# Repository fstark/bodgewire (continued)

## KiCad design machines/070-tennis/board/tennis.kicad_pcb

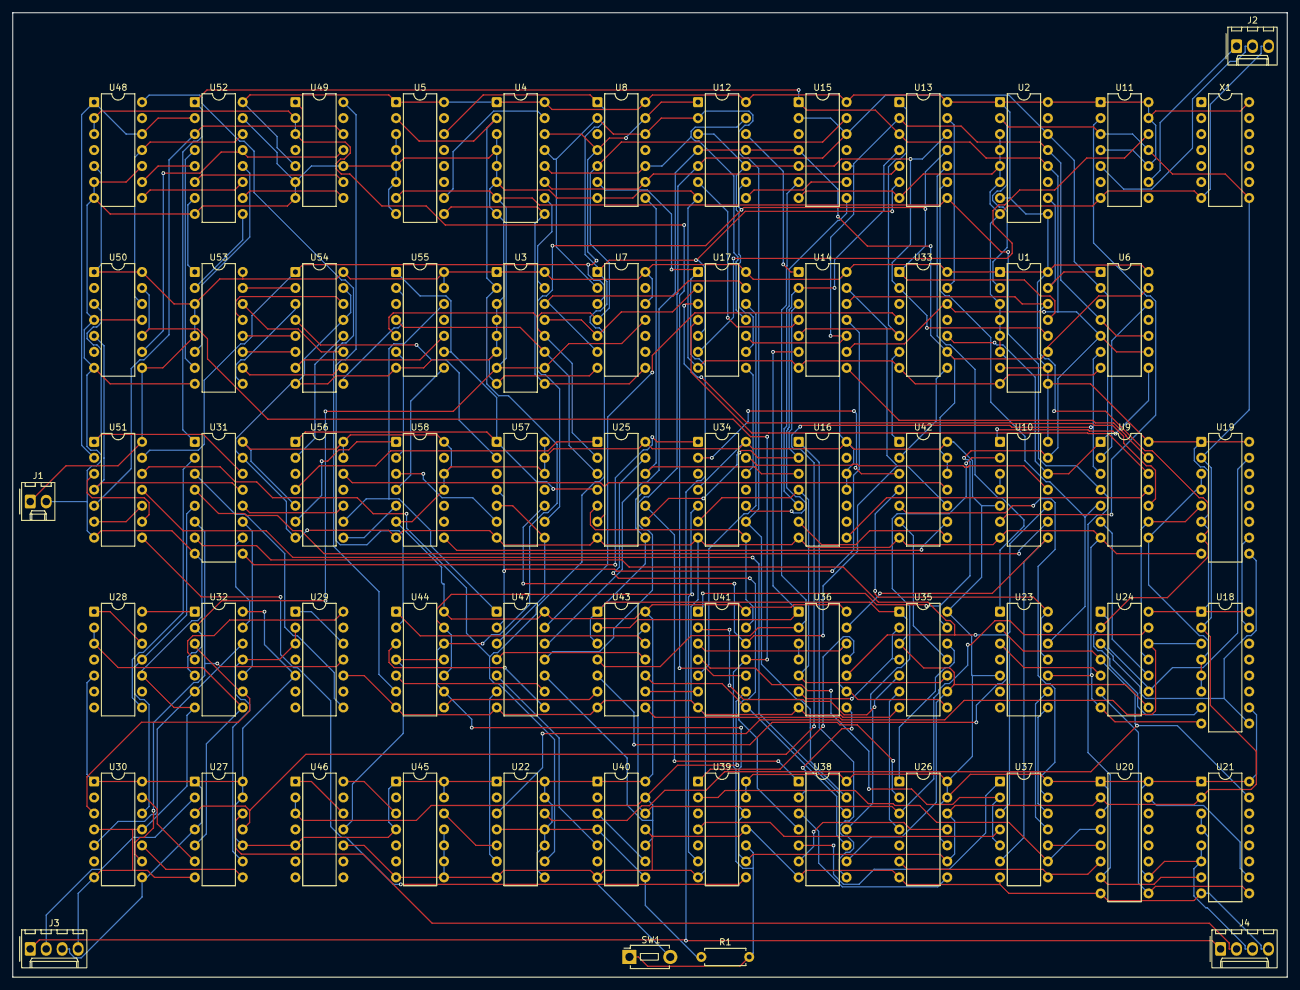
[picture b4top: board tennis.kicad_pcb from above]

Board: 2 copper layers, 202.6 x 153.3 mm, 65 parts (0 on the bottom side), 184 nets.

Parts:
J1: POWER; Molex_KK-254_AE-6410-02A_1x02_P2.54mm_Vertical
J2: VIDEO; Molex_KK-254_AE-6410-03A_1x03_P2.54mm_Vertical
J3, J4: PADDLE; Molex_KK-254_AE-6410-04A_1x04_P2.54mm_Vertical
R1: 1k; R_Axial_DIN0207_L6.3mm_D2.5mm_P7.62mm_Horizontal
SW1: BUTTON; SW_PUSH_1P1T_6x3.5mm_H5.0_APEM_MJTP1250
U1, U2, U3, U4, U5, U18, U19, U20, U21: 74LS161; DIP-16_W7.62mm
U6, U8, U15, U33, U34, U55, U56, U57: 74LS20; DIP-14_W7.62mm
U7, U16, U58: 74LS30; DIP-14_W7.62mm
U9, U41: 74LS04; DIP-14_W7.62mm
U10: 74LS86; DIP-14_W7.62mm
U11, U27: 74LS74; DIP-14_W7.62mm
U12, U17, U35, U43: 74LS27; DIP-14_W7.62mm
U13, U25, U32, U37, U47: 74LS02; DIP-14_W7.62mm
U14, U24, U42, U51: 74LS00; DIP-14_W7.62mm
U22, U26, U30, U39, U40, U44, U45, U50: 74LS107; DIP-14_W7.62mm
U23, U28, U29, U46: 74LS93; DIP-14_W7.62mm
U31, U52, U54: 74LS157; DIP-16_W7.62mm
U36: 74LS08; DIP-14_W7.62mm
U38: 74LS32; DIP-14_W7.62mm
U48, U49: 74LS90; DIP-14_W7.62mm
U53: 74LS48; DIP-16_W7.62mm
X1: OSC; DIP-14_W7.62mm

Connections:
A_TOP: U54.12 (4Y), U56.2 (1B)
BALLV_N: U16.1 (A), U38.8 (3Y)
BALL_CK: U13.10 (3Y), U23.1 (CKB)
BALL_N: U24.8 (3Y), U25.8 (3A), U25.11 (4A), U35.1 (1A), U35.3 (2A), U35.9 (3A), U38.9 (3A), U43.1 (1A), U43.3 (2A)
BALL_OFF: U9.5 (3A), U13.9 (3B), U23.12 (QA)
BALL_QB: U23.9 (QB), U37.11 (4A)
BALL_QC: U23.8 (QC), U37.12 (4B)
BALL_QD: U23.11 (QD), U23.14 (CKA), U42.4 (2A)
BC: U54.7 (2Y), U55.10 (2B)
BHC: U18.15 (RCO), U19.10 (ENT)
BOTTOM_N: U8.8 (2Y), U16.3 (C), U25.12 (4B)
BV8: U22.3 (1Q), U23.3 (R02), U24.5 (2B)
BVC: U20.15 (RCO), U21.10 (ENT)
CLK: U1.2 (CLK), U2.2 (CLK), U3.2 (CLK), U4.2 (CLK), U5.2 (CLK), U11.3 (1CLK), U11.11 (2CLK), U18.2 (CLK), U19.2 (CLK), U20.2 (CLK), U21.2 (CLK), U26.9 (2CLK), U26.12 (1CLK), U39.9 (2CLK), U39.12 (1CLK), U44.9 (2CLK), U44.12 (1CLK), X1.8 (OUT)
COL3: U47.1 (1Y), U55.12 (2C), U56.9 (2A)
COL_L_N: U33.6 (1Y), U42.1 (1A)
COL_R_N: U33.8 (2Y), U42.2 (1B)
FAST: U40.5 (2Q), U47.5 (2A)
FE: U54.4 (1Y), U57.2 (1B)
FRAME0: U22.5 (2Q), U45.12 (1CLK)
FRAME0_N: U22.6 (2Q_N), U47.6 (2B)
FRAME1: U45.3 (1Q), U46.14 (CKA)
FRAME_END_N: U3.9 (LOAD_N), U4.9 (LOAD_N), U5.9 (LOAD_N), U7.8 (Y)
GD: U54.9 (3Y), U55.2 (1B)
GLYPH: U42.9 (3A), U58.8 (Y)
GND: J1.2 (GND), J2.3 (GND), J3.4 (GND), J4.4 (GND), SW1.2, U1.3 (A), U1.4 (B), U1.5 (C), U1.6 (D), U1.8 (GND), U2.3 (A), U2.4 (B), U2.5 (C), U2.6 (D), U2.8 (GND), U3.3 (A), U3.4 (B), U3.5 (C), U3.6 (D), U3.8 (GND), U4.3 (A), U4.4 (B), U4.5 (C), U4.6 (D), U4.8 (GND), U5.3 (A), U5.4 (B), U5.5 (C), U5.6 (D), U5.8 (GND), U6.7 (GND), U7.7 (GND), U8.7 (GND), U9.7 (GND), U10.7 (GND), U11.7 (GND), U12.7 (GND), U13.7 (GND), U14.7 (GND), U15.7 (GND), U16.7 (GND), U17.7 (GND), U18.8 (GND), U19.8 (GND), U20.8 (GND), U21.3 (A), U21.4 (B), U21.8 (GND), U22.7 (GND), U23.10 (GND), U24.7 (GND), U25.7 (GND), U26.7 (GND), U27.7 (GND), U28.10 (GND), U29.10 (GND), U30.4 (1K), U30.7 (GND), U30.11 (2K), U31.8 (GND), U31.15 (G_N), U32.7 (GND), U33.7 (GND), U34.7 (GND), U35.7 (GND), U36.7 (GND), U37.7 (GND), U38.7 (GND), U39.7 (GND), U39.11 (2K), U40.7 (GND), U40.11 (2K), U41.7 (GND), U42.7 (GND), U43.7 (GND), U44.7 (GND), U45.7 (GND), U45.8 (2J), U45.9 (2CLK), U45.10 (2CLR_N), U45.11 (2K), U46.10 (GND), U47.7 (GND), U48.6 (R91), U48.7 (R92), U48.10 (GND), U49.6 (R91), U49.7 (R92), U49.10 (GND), U50.4 (1K), U50.7 (GND), U50.11 (2K), U51.7 (GND), U52.8 (GND), U52.15 (G_N), U53.8 (GND), U54.8 (GND), U54.13 (4B), U54.15 (G_N), U55.7 (GND), U56.7 (GND), U57.7 (GND), U58.7 (GND), X1.7 (GND)
GO_DOWN: U26.8 (2J), U38.3 (1Y)
GO_LEFT: U26.4 (1K), U35.6 (2Y)
GO_RIGHT: U26.1 (1J), U35.12 (1Y)
GO_UP: U26.11 (2K), U38.6 (2Y)
H0: U1.14 (QA), U14.12 (4A), U18.7 (ENP), U19.7 (ENP), U24.2 (1B)
H1: U1.13 (QB), U12.9 (3A), U13.11 (4A), U33.1 (1A), U57.9 (2A)
H2: U1.12 (QC), U12.3 (2A), U12.10 (3B), U13.12 (4B), U15.5 (1D), U17.9 (3A), U33.2 (1B)
H3: U1.11 (QD), U6.13 (2D), U12.4 (2B), U12.11 (3C), U15.4 (1C), U33.9 (2A), U42.12 (4A), U42.13 (4B), U47.12 (4B)
H3_N: U25.6 (2B), U42.11 (4Y), U56.12 (2C)
H4: U2.14 (QA), U6.2 (1B), U9.1 (1A), U10.12 (4A), U12.5 (2C), U15.2 (1B), U15.12 (2C), U33.10 (2B), U47.11 (4A)
H4_N: U6.12 (2C), U9.2 (1Y)
H5: U2.13 (QB), U6.4 (1C), U6.10 (2B), U13.2 (1A), U14.10 (3B), U15.10 (2B), U17.10 (3B)
H6: U2.12 (QC), U6.5 (1D), U6.9 (2A), U10.13 (4B), U13.3 (1B), U14.9 (3A), U15.1 (1A), U31.1 (S), U33.12 (2C), U35.13 (1C), U41.1 (1A), U52.1 (S)
H6_N: U35.5 (2C), U41.2 (1Y)
H12_LOW: U13.13 (4Y), U33.13 (2D)
H34_LOW: U33.4 (1C), U47.13 (4Y)
H56_LOW: U13.1 (1Y), U14.5 (2B), U33.5 (1D)
HBALL: U19.15 (RCO), U24.1 (1A), U24.9 (3A)
HBLANK: U9.12 (6Y), U17.4 (2B)
HBLANK_N: U9.13 (6A), U14.8 (3Y)
HC: U1.15 (RCO), U2.10 (ENT), U6.1 (1A)
HDIR: U24.13 (4B), U26.3 (1Q), U40.12 (1CLK), U43.13 (1C)
HDIR_N: U26.2 (1Q_N), U43.5 (2C)
HIT_BOTTOM: U25.13 (4Y), U38.4 (2A)
HIT_HIGH: U37.1 (1Y), U38.5 (2B)
HIT_LOW: U36.8 (3Y), U38.2 (1B)
HIT_TOP: U25.10 (3Y), U38.1 (1A)
HLOAD_N: U18.9 (LOAD_N), U19.9 (LOAD_N), U24.3 (1Y)
HMOVE: U18.3 (A), U24.12 (4A), U43.8 (3Y)
HSYNC_N: U6.8 (2Y), U10.1 (1A)
HX: U10.11 (4Y), U34.13 (2D)
LDONE: U30.3 (1Q), U32.3 (1B), U32.9 (3B)
LEFT_A: U12.6 (2Y), U14.4 (2A)
LEFT_N: U14.6 (2Y), U36.1 (1A), U43.2 (1B)
LINE_END: U3.7 (ENP), U3.10 (ENT), U4.7 (ENP), U5.7 (ENP), U7.11 (G), U9.4 (2Y), U13.8 (3A), U20.7 (ENP), U21.7 (ENP), U32.2 (1A), U32.5 (2A)
LINE_END_N: U6.6 (1Y), U9.3 (2A), U27.3 (1CLK), U27.11 (2CLK)
LOST_LEFT: U44.3 (1Q), U47.8 (3A)
LOST_LEFT_N: U44.2 (1Q_N), U49.14 (CKA)
LOST_RIGHT: U44.5 (2Q), U47.9 (3B)
LOST_RIGHT_N: U44.6 (2Q_N), U48.14 (CKA)
LP0: U28.1 (CKB), U28.12 (QA)
LP2: U28.8 (QC), U31.2 (1A)
LP3: U28.11 (QD), U30.12 (1CLK), U31.5 (2A)
LPADV: U31.11 (3A), U32.10 (3Y)
LPAD_CK: U28.14 (CKA), U32.1 (1Y)
LPULSE: J3.2 (OUT), U27.2 (1D)
LWAIT: U27.5 (1Q), U28.2 (R01), U28.3 (R02), U32.8 (3A)
LWAIT_N: U27.6 (1Q_N), U30.13 (1CLR_N)
MID_A: U37.13 (4Y), U42.5 (2B)
MID_N: U35.11 (3C), U42.6 (2Y)
MISS_LEFT: U43.12 (1Y), U44.1 (1J)
MISS_RIGHT: U43.6 (2Y), U44.8 (2J)
MIX: U9.11 (5A), U16.8 (Y)
MIX_N: U9.10 (5Y), U17.3 (2A)
MOVE: U17.12 (1Y), U41.5 (3A)
MOVE_N: U41.6 (3Y), U43.9 (3A)
MR: U9.8 (4Y), U18.4 (B), U18.5 (C), U18.6 (D), U19.3 (A), U19.4 (B)
MR_N: U9.9 (4A), U19.5 (C), U24.11 (4Y)
NET_A: U12.8 (3Y), U15.9 (2A)
NET_N: U15.8 (2Y), U16.5 (E)
PADV: U31.9 (3Y), U34.1 (1A)
PAD_HIT: U35.8 (3Y), U36.9 (3A), U36.12 (4A), U41.3 (2A)
PAD_HIT_N: U37.2 (1A), U37.5 (2A), U41.4 (2Y)
PAD_N: U16.4 (D), U34.6 (1Y), U35.10 (3B), U36.5 (2B)
PCOL: U34.2 (1B), U42.3 (1Y)
PLAY: U34.5 (1D), U39.6 (2Q_N), U44.10 (2CLR_N), U44.13 (1CLR_N)
QH0_N: U14.11 (4Y), U47.2 (1A), U57.4 (1C)
QH1_N: U47.3 (1B), U57.5 (1D), U57.8 (2Y)
RDONE: U30.5 (2Q), U32.6 (2B), U32.12 (4B)
REGION: U14.13 (4B), U41.12 (6Y), U42.10 (3B), U57.10 (2B)
REGION_N: U25.5 (2A), U34.8 (2Y), U41.13 (6A)
RIGHT_N: U15.6 (1Y), U36.2 (1B), U43.4 (2B)
RP0: U29.1 (CKB), U29.12 (QA)
RP2: U29.8 (QC), U31.3 (1B)
RP3: U29.11 (QD), U30.9 (2CLK), U31.6 (2B)
RPADV: U31.10 (3B), U32.13 (4Y)
RPAD_CK: U29.14 (CKA), U32.4 (2Y)
RPULSE: J4.2 (OUT), U27.12 (2D)
RWAIT: U27.9 (2Q), U29.2 (R01), U29.3 (R02), U32.11 (4A)
RWAIT_N: U27.8 (2Q_N), U30.10 (2CLR_N)
SC0: U52.4 (1Y), U53.7 (A)
SC1: U52.7 (2Y), U53.1 (B)
SC2: U52.9 (3Y), U53.2 (C)
SC3: U52.12 (4Y), U53.6 (D)
SCORE_A: U17.8 (3Y), U34.12 (2C)
SCORE_N: U16.6 (F), U42.8 (3Y)
SEG_A: U53.13 (SA), U54.14 (4A)
SEG_B: U53.12 (SB), U54.5 (2A)
SEG_C: U53.11 (SC), U54.6 (2B)
SEG_D: U53.10 (SD), U54.10 (3B)
SEG_E: U53.9 (SE), U54.3 (1B)
SEG_F: U53.15 (SF), U54.2 (1A)
SEG_G: U53.14 (SG), U54.11 (3A)
SERVE_END: U44.4 (1K), U44.11 (2K), U46.11 (QD)
SERVING: U38.10 (3B), U41.8 (4Y), U43.10 (3B)
SERVING_N: U40.10 (2CLR_N), U40.13 (1CLR_N), U41.9 (4A), U46.2 (R01), U46.3 (R02), U47.10 (3Y)
SET_SHALLOW: U36.11 (4Y), U39.1 (1J)
SET_STEEP: U37.4 (2Y), U39.4 (1K)
SIDES_N: U36.3 (1Y), U36.4 (2A)
SKIP: U43.11 (3C), U47.4 (2Y)
SL0: U48.1 (CKB), U48.12 (QA), U51.2 (1B), U52.2 (1A)
SL1: U48.9 (QB), U52.5 (2A)
SL2: U48.8 (QC), U52.11 (3A)
SL3: U48.11 (QD), U50.12 (1CLK), U52.14 (4A)
SP2: U10.9 (3A), U31.4 (1Y)
SP3: U10.10 (3B), U31.7 (2Y), U36.10 (3B), U37.3 (1B)
SP_MID: U10.8 (3Y), U36.13 (4B), U37.6 (2B)
SR0: U49.1 (CKB), U49.12 (QA), U51.5 (2B), U52.3 (1B)
SR1: U49.9 (QB), U52.6 (2B)
SR2: U49.8 (QC), U52.10 (3B)
SR3: U49.11 (QD), U50.9 (2CLK), U52.13 (4B)
ST0: U46.1 (CKB), U46.12 (QA)
START: U41.10 (5Y), U48.2 (R01), U48.3 (R02), U49.2 (R01), U49.3 (R02)
START_N: R1.2, SW1.1, U39.10 (2CLR_N), U41.11 (5A), U50.10 (2CLR_N), U50.13 (1CLR_N)
STEEP: U20.4 (B), U37.9 (3B), U39.2 (1Q_N)
SYNC: U10.3 (1Y), U10.4 (2A)
SYNC_N: J2.2 (SYNC_N), U11.5 (1Q)
SYNC_N_D: U10.6 (2Y), U11.2 (1D)
T1_N: U56.6 (1Y), U58.1 (A)
T2_N: U55.6 (1Y), U58.2 (B)
T3_N: U57.6 (1Y), U58.3 (C)
T4_N: U55.8 (2Y), U58.4 (D)
T5_N: U56.8 (2Y), U58.5 (E)
TENS: U31.12 (4Y), U56.10 (2B)
TENS_L: U31.14 (4A), U50.3 (1Q), U51.1 (1A)
TENS_R: U31.13 (4B), U50.5 (2Q), U51.4 (2A)
TICK_N: J3.1 (TRIG_N), J4.1 (TRIG_N), U8.6 (1Y), U17.1 (1A)
TOP_A: U12.12 (1Y), U14.1 (1A)
TOP_B: U13.4 (2Y), U14.2 (1B), U34.10 (2B)
TOP_N: U14.3 (1Y), U16.2 (B), U25.9 (3B)
TURN_N: U35.2 (1B), U35.4 (2B), U36.6 (2Y)
TURN_ODD: U40.3 (1Q), U40.9 (2CLK)
UNITS: U25.4 (2Y), U55.1 (1A), U55.9 (2A), U56.1 (1A), U57.1 (1A)
V0: U3.14 (QA), U7.6 (F), U17.13 (1C)
V1: U3.13 (QB), U7.5 (E), U17.2 (1B)
V2: U3.12 (QC), U7.4 (D), U8.5 (1D), U15.13 (2D), U25.2 (1A), U55.5 (1D)
V3: U3.11 (QD), U25.3 (1B), U55.4 (1C)
V4: U4.14 (QA), U7.3 (C), U8.4 (1C), U8.13 (2D), U12.1 (1A), U51.13 (4B), U54.1 (S)
V5: U4.13 (QB), U7.2 (B), U8.2 (1B), U8.12 (2C), U12.2 (1B), U34.9 (2A), U38.13 (4B)
V6: U4.12 (QC), U8.10 (2B), U12.13 (1C), U17.11 (3C)
V7: U4.11 (QD), U8.9 (2A), U13.5 (2A)
V8: U5.14 (QA), U7.1 (A), U8.1 (1A), U13.6 (2B), U17.5 (2C), U22.9 (2CLK), U51.12 (4A)
V23_LOW: U25.1 (1Y), U56.4 (1C)
VBALL: U9.6 (3Y), U24.10 (3B)
VC1: U3.15 (RCO), U4.10 (ENT)
VC2: U4.15 (RCO), U5.10 (ENT)
VCC: J1.1 (VCC), J3.3 (VCC), J4.3 (VCC), R1.1, U1.1 (CLR_N), U1.7 (ENP), U1.9 (LOAD_N), U1.10 (ENT), U1.16 (VCC), U2.1 (CLR_N), U2.7 (ENP), U2.9 (LOAD_N), U2.16 (VCC), U3.1 (CLR_N), U3.16 (VCC), U4.1 (CLR_N), U4.16 (VCC), U5.1 (CLR_N), U5.16 (VCC), U6.14 (VCC), U7.12 (H), U7.14 (VCC), U8.14 (VCC), U9.14 (VCC), U10.5 (2B), U10.14 (VCC), U11.1 (1CLR_N), U11.4 (1PRE_N), U11.10 (2PRE_N), U11.13 (2CLR_N), U11.14 (VCC), U12.14 (VCC), U13.14 (VCC), U14.14 (VCC), U15.14 (VCC), U16.11 (G), U16.12 (H), U16.14 (VCC), U17.14 (VCC), U18.1 (CLR_N), U18.10 (ENT), U18.16 (VCC), U19.1 (CLR_N), U19.6 (D), U19.16 (VCC), U20.1 (CLR_N), U20.3 (A), U20.10 (ENT), U20.16 (VCC), U21.1 (CLR_N), U21.5 (C), U21.6 (D), U21.16 (VCC), U22.1 (1J), U22.4 (1K), U22.8 (2J), U22.10 (2CLR_N), U22.11 (2K), U22.13 (1CLR_N), U22.14 (VCC), U23.5 (VCC), U24.14 (VCC), U25.14 (VCC), U26.10 (2CLR_N), U26.13 (1CLR_N), U26.14 (VCC), U27.1 (1CLR_N), U27.4 (1PRE_N), U27.10 (2PRE_N), U27.13 (2CLR_N), U27.14 (VCC), U28.5 (VCC), U29.5 (VCC), U30.1 (1J), U30.8 (2J), U30.14 (VCC), U31.16 (VCC), U32.14 (VCC), U33.14 (VCC), U34.4 (1C), U34.14 (VCC), U35.14 (VCC), U36.14 (VCC), U37.14 (VCC), U38.14 (VCC), U39.13 (1CLR_N), U39.14 (VCC), U40.1 (1J), U40.4 (1K), U40.8 (2J), U40.14 (VCC), U41.14 (VCC), U42.14 (VCC), U43.14 (VCC), U44.14 (VCC), U45.1 (1J), U45.4 (1K), U45.13 (1CLR_N), U45.14 (VCC), U46.5 (VCC), U47.14 (VCC), U48.5 (VCC), U49.5 (VCC), U50.1 (1J), U50.8 (2J), U50.14 (VCC), U51.14 (VCC), U52.16 (VCC), U53.3 (LT_N), U53.4 (BI_N), U53.5 (RBI_N), U53.16 (VCC), U54.16 (VCC), U55.13 (2D), U55.14 (VCC), U56.5 (1D), U56.13 (2D), U56.14 (VCC), U57.12 (2C), U57.13 (2D), U57.14 (VCC), U58.6 (F), U58.11 (G), U58.12 (H), U58.14 (VCC), X1.14 (VCC)
VDIR_N: U20.6 (D), U26.6 (2Q_N), U37.8 (3A)
VIDEO: J2.1 (VIDEO), U11.9 (2Q)
VIDEO_D: U11.12 (2D), U17.6 (2Y)
VLOAD_C: U20.5 (C), U37.10 (3Y)
VLOAD_N: U20.9 (LOAD_N), U21.9 (LOAD_N), U24.6 (2Y)
VRCO: U21.15 (RCO), U22.12 (1CLK), U23.2 (R01), U24.4 (2A)
VSYNC_A: U38.12 (4A), U51.11
VSYNC_N: U10.2 (1B), U38.11
WIN: U39.8 (2J), U51.8 (3Y)
WIN_L_N: U51.3 (1Y), U51.9 (3A)
WIN_R_N: U51.6 (2Y), U51.10 (3B)

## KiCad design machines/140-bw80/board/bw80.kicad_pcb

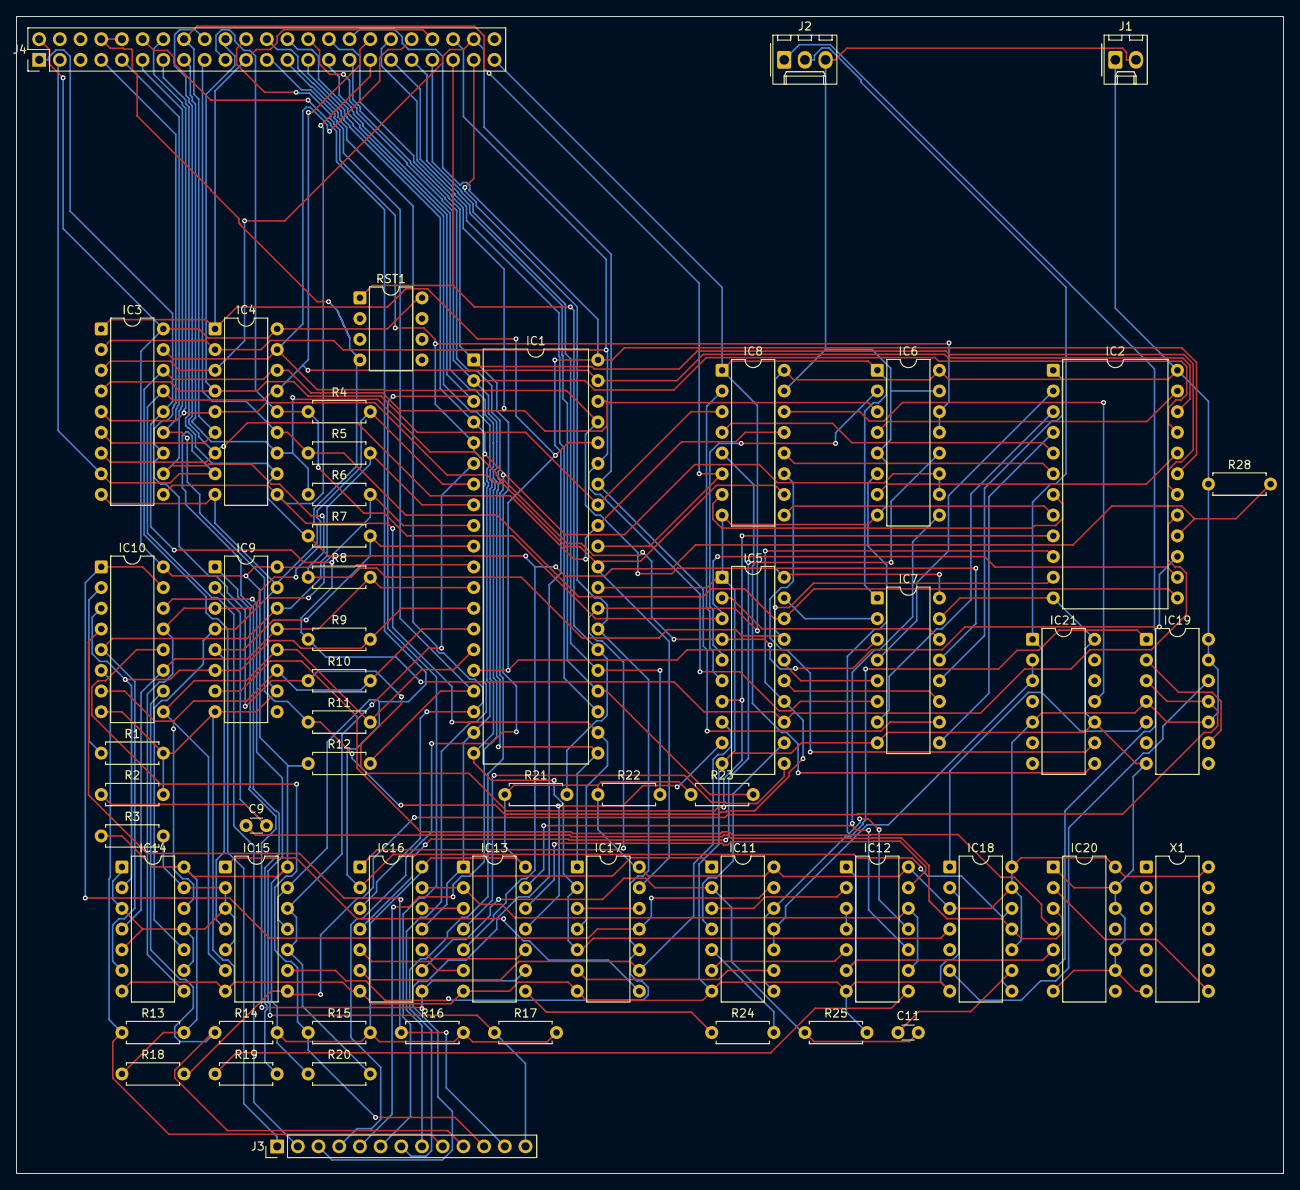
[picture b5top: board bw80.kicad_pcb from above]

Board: 2 copper layers, 155.5 x 142.0 mm, 55 parts (0 on the bottom side), 112 nets.

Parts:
C9, C11: 47p; C_Disc_D3.0mm_W1.6mm_P2.50mm
IC1: Z80; DIP-40_W15.24mm
IC2: 2332; DIP-24_W15.24mm
IC3, IC4: 2114; DIP-18_W7.62mm
IC5: 74LS373; DIP-20_W7.62mm
IC6, IC7, IC8: 74LS157; DIP-16_W7.62mm
IC9: 74LS165; DIP-16_W7.62mm
IC10: 74LS365; DIP-16_W7.62mm
IC11, IC12: 74LS00; DIP-14_W7.62mm
IC13: 74LS04; DIP-14_W7.62mm
IC14, IC15: 74LS05; DIP-14_W7.62mm
IC16: 74LS10; DIP-14_W7.62mm
IC17: 74LS32; DIP-14_W7.62mm
IC18, IC19: 74LS74; DIP-14_W7.62mm
IC20: 74LS86; DIP-14_W7.62mm
IC21: 74LS93; DIP-14_W7.62mm
J1: POWER; Molex_KK-254_AE-6410-02A_1x02_P2.54mm_Vertical
J2: VIDEO; Molex_KK-254_AE-6410-03A_1x03_P2.54mm_Vertical
J3: BW80KB; PinHeader_1x13_P2.54mm_Vertical
J4: EXPANSION; PinHeader_2x23_P2.54mm_Vertical
R1, R3, R4, R5, R6, R7, R8, R9, R10, R11, R12, R18, R22, R23, R24: 1k; R_Axial_DIN0207_L6.3mm_D2.5mm_P7.62mm_Horizontal
R2, R25: 470; R_Axial_DIN0207_L6.3mm_D2.5mm_P7.62mm_Horizontal
R13, R14, R15, R16, R17, R28: 47k; R_Axial_DIN0207_L6.3mm_D2.5mm_P7.62mm_Horizontal
R19: 2k2; R_Axial_DIN0207_L6.3mm_D2.5mm_P7.62mm_Horizontal
R20: 330; R_Axial_DIN0207_L6.3mm_D2.5mm_P7.62mm_Horizontal
R21: 220k; R_Axial_DIN0207_L6.3mm_D2.5mm_P7.62mm_Horizontal
RST1: POR; DIP-8_W7.62mm
X1: OSC; DIP-14_W7.62mm

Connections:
A0: IC1.30 (A0), IC3.5 (A0), IC4.5 (A0), IC8.10 (3B), IC17.13 (4B), J4.14 (A0)
A1: IC1.31 (A1), IC3.6 (A1), IC4.6 (A1), IC8.6 (2B), J4.16 (A1)
A2: IC1.32 (A2), IC3.7 (A2), IC4.7 (A2), IC8.13 (4B), J4.18 (A2)
A3: IC1.33 (A3), IC3.4 (A3), IC4.4 (A3), IC8.3 (1B), J4.20 (A3)
A4: IC1.34 (A4), IC3.3 (A4), IC4.3 (A4), IC7.10 (3B), J4.44 (A4)
A5: IC1.35 (A5), IC3.2 (A5), IC4.2 (A5), IC7.6 (2B), J4.42 (A5)
A6: IC1.16 (INT_N), IC1.36 (A6), IC3.1 (A6), IC4.1 (A6), IC7.3 (1B), J4.21 (INT_N), J4.40 (A6)
A7: IC1.37 (A7), IC3.17 (A7), IC4.17 (A7), IC7.13 (4B), J4.38 (A7)
A8: IC1.38 (A8), IC3.16 (A8), IC4.16 (A8), IC6.3 (1B), J3.1 (A8), J4.36 (A8)
A9: IC1.39 (A9), IC2.22 (A9), IC3.15 (A9), IC4.15 (A9), J3.2 (A9), J4.34 (A9)
A10: IC1.40 (A10), IC2.19 (A10), J3.3 (A10), J4.32 (A10)
A11: IC1.1 (A11), IC2.18 (A11), J3.4 (A11), J4.30 (A11)
A12: IC1.2 (A12), IC2.21 (CS2), J3.5 (A12), J4.28 (A12)
A13: IC1.3 (A13), J3.6 (A13), J4.26 (A13)
A14: IC1.4 (A14), IC6.10 (3B), IC6.11 (3A), J3.7 (A14), J4.24 (A14)
A14B: IC6.9 (3Y), IC12.10 (3B), IC13.13 (6A)
A14B_N: IC12.13 (4B), IC13.12 (6Y)
A15: IC1.5 (A15), IC6.13 (4B), IC6.14 (4A), J3.8 (A15), J4.22 (A15)
A15B: IC6.12 (4Y), IC16.4 (2B)
BUSAK_N: IC1.23 (BUSAK_N), J4.35 (BUSAK_N)
BUSRQ_N: IC1.25 (BUSRQ_N), J4.39 (BUSRQ_N), R22.2
CH0: IC5.6 (3Q), IC8.2 (1A)
CH1: IC5.15 (6Q), IC7.11 (3A)
CH2: IC5.16 (7Q), IC7.5 (2A)
CH3: IC5.19 (8Q), IC7.2 (1A)
CH4: IC5.2 (1Q), IC7.14 (4A)
CH5: IC5.5 (2Q), IC6.2 (1A)
CH7: IC5.12 (5Q), IC11.4 (2A)
CHAR_FETCH: IC13.10 (5Y), IC16.10 (3B)
CHAR_FETCH_N: IC5.9 (4Q), IC13.11 (5A)
CLK: IC1.6 (CLK), IC15.10 (5Y), IC15.12 (6Y), R20.2
D0: IC1.14 (D0), IC9.11 (A), IC10.7 (Y3), IC14.12 (6Y), R10.2
D1: IC1.15 (D1), IC9.12 (B), IC10.9 (Y4), IC15.6 (3Y), R11.2
D2: IC1.12 (D2), IC9.13 (C), IC10.11 (Y5), IC14.4 (2Y), R8.2
D3: IC1.8 (D3), IC9.14 (D), IC10.5 (Y2), IC14.6 (3Y), R5.2
D4: IC1.7 (D4), IC9.3 (E), IC10.13 (Y6), IC14.8 (4Y), R4.2
D5: IC1.9 (D5), IC9.4 (F), IC14.10 (5Y), R6.2
D6: IC1.10 (D6), IC9.5 (G), IC15.4 (2Y), R7.2
D7: IC1.13 (D7), IC9.6 (H), IC10.3 (Y1), IC14.2 (1Y), R9.2
DOT: IC20.2 (1B), X1.8 (OUT)
DOT2: C9.1, IC18.11 (2CLK), IC20.3 (1Y)
EAR: IC10.2 (A1), R1.1
GND: IC1.29 (GND), IC2.12 (GND), IC3.9 (GND), IC4.9 (GND), IC5.1 (OE_N), IC5.10 (GND), IC6.5 (2A), IC6.8 (GND), IC6.15 (G_N), IC7.8 (GND), IC7.15 (G_N), IC8.8 (GND), IC8.15 (G_N), IC9.8 (GND), IC9.10 (SER), IC9.15 (CLK_INH), IC10.8 (GND), IC11.7 (GND), IC12.7 (GND), IC13.7 (GND), IC14.7 (GND), IC15.7 (GND), IC16.7 (GND), IC17.7 (GND), IC18.2 (1D), IC18.7 (GND), IC19.7 (GND), IC20.1 (1A), IC20.7 (GND), IC20.9 (3A), IC20.10 (3B), IC20.12 (4A), IC20.13 (4B), IC21.10 (GND), IC21.14 (CKA), J1.2 (GND), J2.3 (GND), J4.8 (GND1), J4.10 (GND2), R1.2, R2.2, R25.2, RST1.4 (GND), X1.7 (GND)
HALT_N: IC1.18 (HALT_N), IC16.3 (2A), J4.25 (HALT_N)
INV: IC12.1 (1A), IC12.6 (2Y), IC20.5 (2B)
INV_N: IC12.3 (1Y), IC12.4 (2A)
INV_SET_N: IC11.6 (2Y), IC12.5 (2B)
INV_STROBE_N: IC11.3 (1Y), IC12.2 (1B)
IORD_N: IC17.3 (1Y), IC17.12 (4A)
IORQ_N: IC1.20 (IORQ_N), IC17.2 (1B), IC17.5 (2B), IC18.4 (1PRE_N), J4.29 (IORQ_N)
IOWR_N: IC11.9 (3A), IC17.6 (2Y)
KB0: IC10.6 (A3), J3.9 (KB0), R13.1
KB1: IC10.10 (A4), J3.10 (KB1), R14.1
KB2: IC10.12 (A5), J3.11 (KB2), R15.1
KB3: IC10.4 (A2), J3.12 (KB3), R16.1
KB4: IC10.14 (A6), J3.13 (KB4), R17.1
KBD_N: IC10.1 (G1_N), IC10.15 (G2_N), IC11.13 (4B), IC17.11 (4Y)
LC0: IC8.11 (3A), IC21.9 (QB)
LC1: IC8.5 (2A), IC21.8 (QC)
LC2: IC8.14 (4A), IC21.11 (QD)
LE: IC5.11 (LE), IC13.4 (2Y)
LE_N: IC13.3 (2A), IC16.12 (1Y)
LOAD: IC13.8 (4Y), R24.1
LOAD_N: IC9.1 (SH_LD_N), IC13.9 (4A), IC16.8 (3Y)
LOAD_PULSE: C11.2, IC11.2 (1B), IC16.9 (3A), R25.1
LOAD_R: IC11.5 (2B), R24.2
M1_CLK: IC15.8 (4Y), IC19.3 (1CLK), IC19.11 (2CLK), R18.2
M1_N: IC1.27 (M1_N), IC15.9 (4A), IC17.10 (3B), J4.43 (M1_N)
MD0: IC2.9 (O0), IC3.12 (IO3), IC5.7 (3D), J4.7 (D0), R10.1
MD1: IC2.10 (O1), IC3.13 (IO2), IC5.14 (6D), J4.9 (D1), R11.1
MD2: IC2.11 (O2), IC3.11 (IO4), IC5.17 (7D), J4.11 (D2), R8.1
MD3: IC2.13 (O3), IC4.13 (IO2), IC5.18 (8D), J4.17 (D3), R5.1
MD4: IC2.14 (O4), IC4.14 (IO1), IC5.3 (1D), J4.19 (D4), R4.1
MD5: IC2.15 (O5), IC4.12 (IO3), IC5.4 (2D), J4.15 (D5), R6.1
MD6: IC2.16 (O6), IC4.11 (IO4), IC13.5 (3A), J4.13 (D6), R7.1, R28.2
MD6_N: IC13.6 (3Y), IC16.5 (2C)
MD7: IC2.17 (O7), IC3.14 (IO1), IC5.13 (5D), J4.1 (D7), R9.1
MREQ: IC12.9 (3A), IC12.12 (4A), IC13.2 (1Y), IC16.13 (1C)
MREQ_N: IC1.19 (MREQ_N), IC11.1 (1A), IC13.1 (1A), IC16.11 (3C), J4.27 (MREQ_N)
NMI_N: IC1.17 (NMI_N), J4.23 (NMI_N), R12.2
NOP_COND_N: IC5.8 (4D), IC16.6 (2Y), IC17.9 (3A)
NOP_EN: IC14.1 (1A), IC14.3 (2A), IC14.5 (3A), IC14.9 (4A), IC14.11 (5A), IC14.13 (6A), IC15.2 (1Y), IC15.3 (2A), IC15.5 (3A), R3.2
NOP_N: IC15.1 (1A), IC17.8 (3Y)
PHI: C11.1, IC18.9 (2Q)
PHI_N: IC15.11 (5A), IC15.13 (6A), IC16.2 (1B), IC18.8 (2Q_N), IC18.12 (2D), J4.12 (PHI)
PIX_N: IC9.7 (QH_N), IC20.4 (2A)
RA0: IC2.8 (A0), IC8.9 (3Y)
RA1: IC2.7 (A1), IC8.7 (2Y)
RA2: IC2.6 (A2), IC8.12 (4Y)
RA3: IC2.5 (A3), IC8.4 (1Y)
RA4: IC2.4 (A4), IC7.9 (3Y)
RA5: IC2.3 (A5), IC7.7 (2Y)
RA6: IC2.2 (A6), IC7.4 (1Y)
RA7: IC2.1 (A7), IC7.12 (4Y)
RA8: IC2.23 (A8), IC6.4 (1Y)
RAM_CS_N: IC3.8 (CS_N), IC4.8 (CS_N), J4.3 (RAMCS_N), R19.2
RAM_SEL_N: IC12.8 (3Y), R19.1
RD_N: IC1.21 (RD_N), IC17.1 (1A), J4.31 (RD_N)
RESET_N: IC1.26 (RESET_N), J4.41 (RESET_N), R21.2, RST1.1 (RST_N)
RFSH_N: IC1.28 (RFSH_N), IC6.1 (S), IC7.1 (S), IC8.1 (S), IC16.1 (1A), J4.45 (RFSH_N)
ROM_CS1: IC2.20 (CS1), IC6.7 (2Y)
ROM_SEL_N: IC6.6 (2B), IC12.11 (4Y)
SHIFT_CLK: C9.2, IC9.2 (CLK), R2.1
SYNC: IC18.1 (1CLR_N), IC19.5 (1Q), IC21.1 (CKB), J2.2 (SYNC_N)
SYNC_ARM_N: IC18.6 (1Q_N), IC19.12 (2D)
SYNC_NEXT: IC19.2 (1D), IC19.9 (2Q)
VCC: IC1.11 (VCC), IC2.24 (VCC), IC3.18 (VCC), IC4.18 (VCC), IC5.20 (VCC), IC6.16 (VCC), IC7.16 (VCC), IC8.16 (VCC), IC9.16 (VCC), IC10.16 (VCC), IC11.14 (VCC), IC12.14 (VCC), IC13.14 (VCC), IC14.14 (VCC), IC15.14 (VCC), IC16.14 (VCC), IC17.14 (VCC), IC18.3 (1CLK), IC18.10 (2PRE_N), IC18.13 (2CLR_N), IC18.14 (VCC), IC19.4 (1PRE_N), IC19.10 (2PRE_N), IC19.13 (2CLR_N), IC19.14 (VCC), IC20.14 (VCC), IC21.5 (VCC), J1.1 (VCC), J4.2 (VCC5), R3.1, R12.1, R13.2, R14.2, R15.2, R16.2, R17.2, R18.1, R20.1, R21.1, R22.1, R23.1, R28.1, RST1.8 (VCC), X1.14 (VCC)
VIDEO: IC20.6 (2Y), J2.1 (VIDEO)
VS_N: IC11.8 (3Y), IC11.12 (4A), IC19.1 (1CLR_N)
VS_RESET: IC11.10 (3B), IC11.11 (4Y), IC21.2 (R01), IC21.3 (R02)
WAIT_N: IC1.24 (WAIT_N), J4.37 (WAIT_N), R23.2
WR_N: IC1.22 (WR_N), IC3.10 (WE_N), IC4.10 (WE_N), IC17.4 (2A), J4.33 (WR_N)

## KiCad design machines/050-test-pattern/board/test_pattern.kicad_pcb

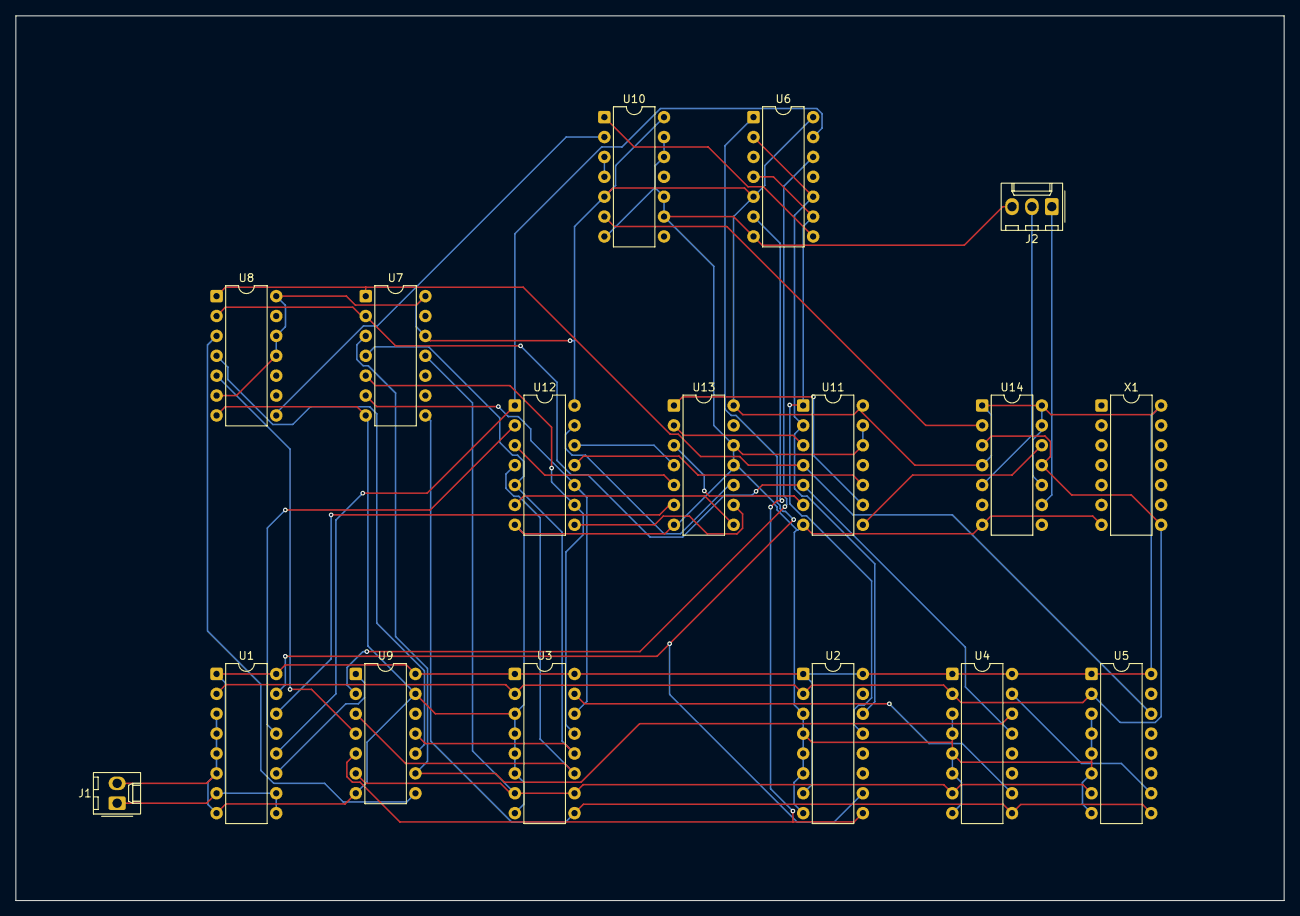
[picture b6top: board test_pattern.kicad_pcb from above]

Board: 2 copper layers, 162.0 x 113.0 mm, 17 parts (0 on the bottom side), 42 nets.

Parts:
J1: POWER; Molex_KK-254_AE-6410-02A_1x02_P2.54mm_Vertical
J2: VIDEO; Molex_KK-254_AE-6410-03A_1x03_P2.54mm_Vertical
U1, U2, U3, U4, U5: 74LS161; DIP-16_W7.62mm
U6: 74LS20; DIP-14_W7.62mm
U7, U8: 74LS30; DIP-14_W7.62mm
U9: 74LS04; DIP-14_W7.62mm
U10: 74LS86; DIP-14_W7.62mm
U11: 74LS08; DIP-14_W7.62mm
U12: 74LS32; DIP-14_W7.62mm
U13: 74LS02; DIP-14_W7.62mm
U14: 74LS74; DIP-14_W7.62mm
X1: OSC; DIP-14_W7.62mm

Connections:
ACTIVE: U11.9 (3A), U13.1 (1Y)
CLK: U1.2 (CLK), U2.2 (CLK), U3.2 (CLK), U4.2 (CLK), U5.2 (CLK), U14.3 (1CLK), U14.11 (2CLK), X1.8 (OUT)
FRAME_END_N: U3.9 (LOAD_N), U4.9 (LOAD_N), U5.9 (LOAD_N), U7.8 (Y)
GND: J1.2 (GND), J2.3 (GND), U1.3 (A), U1.4 (B), U1.5 (C), U1.6 (D), U1.8 (GND), U2.3 (A), U2.4 (B), U2.5 (C), U2.6 (D), U2.8 (GND), U3.3 (A), U3.4 (B), U3.5 (C), U3.6 (D), U3.8 (GND), U4.3 (A), U4.4 (B), U4.5 (C), U4.6 (D), U4.8 (GND), U5.3 (A), U5.4 (B), U5.5 (C), U5.6 (D), U5.8 (GND), U6.7 (GND), U7.7 (GND), U8.7 (GND), U9.7 (GND), U9.13 (6A), U10.7 (GND), U10.9 (3A), U10.10 (3B), U10.12 (4A), U10.13 (4B), U11.7 (GND), U11.12 (4A), U11.13 (4B), U12.7 (GND), U13.7 (GND), U13.11 (4A), U13.12 (4B), U14.7 (GND), X1.7 (GND)
GRID: U11.10 (3B), U12.11 (4Y)
GRIDH: U12.12 (4A), U13.4 (2Y)
GRIDV: U12.13 (4B), U13.10 (3Y)
H0: U1.14 (QA), U13.6 (2B)
H1: U1.13 (QB), U12.2 (1B)
H2: U1.12 (QC), U6.13 (2D), U12.1 (1A)
H3: U1.11 (QD), U9.1 (1A)
H3_N: U6.12 (2C), U9.2 (1Y)
H4: U2.14 (QA), U6.2 (1B), U6.10 (2B), U11.2 (1B)
H5: U2.13 (QB), U6.4 (1C), U6.9 (2A), U11.1 (1A)
H21: U12.3 (1Y), U13.5 (2A)
HBLANK: U11.3 (1Y), U13.2 (1A)
HC: U1.15 (RCO), U2.10 (ENT), U6.1 (1A)
HSYNC_N: U6.8 (2Y), U10.1 (1A)
LINE_END: U3.7 (ENP), U3.10 (ENT), U4.7 (ENP), U5.7 (ENP), U7.11 (G), U9.6 (3Y)
LINE_END_N: U2.9 (LOAD_N), U6.6 (1Y), U9.5 (3A)
SYNC: U10.3 (1Y), U10.4 (2A)
SYNC_N: J2.2 (SYNC_N), U14.5 (1Q)
SYNC_N_D: U10.6 (2Y), U14.2 (1D)
V0: U3.14 (QA), U7.6 (F), U12.10 (3B)
V1: U3.13 (QB), U7.5 (E), U12.9 (3A)
V2: U3.12 (QC), U7.4 (D), U9.11 (5A), U12.5 (2B)
V2_N: U8.4 (D), U9.10 (5Y)
V3: U3.11 (QD), U9.3 (2A), U12.4 (2A)
V3_N: U8.5 (E), U9.4 (2Y)
V4: U4.14 (QA), U7.3 (C), U9.9 (4A)
V4_N: U8.3 (C), U9.8 (4Y)
V5: U4.13 (QB), U7.2 (B), U8.2 (B), U11.5 (2B)
V8: U5.14 (QA), U7.1 (A), U8.1 (A), U11.4 (2A)
V10: U12.8 (3Y), U13.9 (3B)
V32: U12.6 (2Y), U13.8 (3A)
VBLANK: U11.6 (2Y), U13.3 (1B)
VC1: U3.15 (RCO), U4.10 (ENT)
VC2: U4.15 (RCO), U5.10 (ENT)
VCC: J1.1 (VCC), U1.1 (CLR_N), U1.7 (ENP), U1.9 (LOAD_N), U1.10 (ENT), U1.16 (VCC), U2.1 (CLR_N), U2.7 (ENP), U2.16 (VCC), U3.1 (CLR_N), U3.16 (VCC), U4.1 (CLR_N), U4.16 (VCC), U5.1 (CLR_N), U5.16 (VCC), U6.5 (1D), U6.14 (VCC), U7.12 (H), U7.14 (VCC), U8.6 (F), U8.11 (G), U8.12 (H), U8.14 (VCC), U9.14 (VCC), U10.5 (2B), U10.14 (VCC), U11.14 (VCC), U12.14 (VCC), U13.14 (VCC), U14.1 (1CLR_N), U14.4 (1PRE_N), U14.10 (2PRE_N), U14.13 (2CLR_N), U14.14 (VCC), X1.14 (VCC)
VIDEO: J2.1 (VIDEO), U14.9 (2Q)
VIDEO_D: U11.8 (3Y), U14.12 (2D)
VSYNC_N: U8.8 (Y), U10.2 (1B)
